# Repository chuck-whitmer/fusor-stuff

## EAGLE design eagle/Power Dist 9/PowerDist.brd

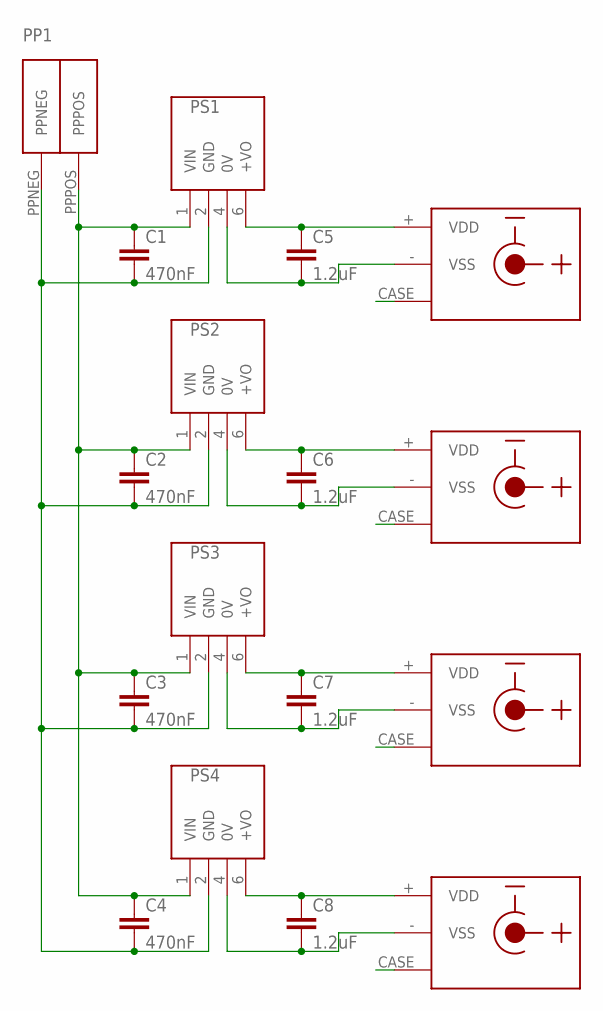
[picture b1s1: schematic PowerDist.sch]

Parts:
C1, C2, C3, C4: 470nF; C5B2.5
C5, C6, C7, C8: 1.2uF; C2.5-3
PP1: POWER_POLES_WINGS; POWERPOLE_PAIR_WINGS
PS1, PS2, PS3, PS4: PRMCE1-S12-S15-S; PRMCE1S12S15S
U$1, U$2, U$3, U$4: CUI_PJ-102A; CUI_DCJACK_PCB

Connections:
CASE: U$1.CASE
CASE1: U$2.CASE
CASE2: U$3.CASE
CASE3: U$4.CASE
unnamed: C1.1, C2.1, C3.1, C4.1, PP1.PPPOS, PS1.1 (VIN), PS2.1 (VIN), PS3.1 (VIN), PS4.1 (VIN)
unnamed: C1.2, C2.2, C3.2, C4.2, PP1.PPNEG, PS1.2 (GND), PS2.2 (GND), PS3.2 (GND), PS4.2 (GND)
unnamed: C5.1, PS1.6 (+VO), U$1.+ (VDD)
unnamed: C6.1, PS2.6 (+VO), U$2.+ (VDD)
unnamed: C7.1, PS3.6 (+VO), U$3.+ (VDD)
unnamed: C8.1, PS4.6 (+VO), U$4.+ (VDD)
unnamed: C5.2, PS1.4 (0V), U$1.- (VSS)
unnamed: C6.2, PS2.4 (0V), U$2.- (VSS)
unnamed: C7.2, PS3.4 (0V), U$3.- (VSS)
unnamed: C8.2, PS4.4 (0V), U$4.- (VSS)

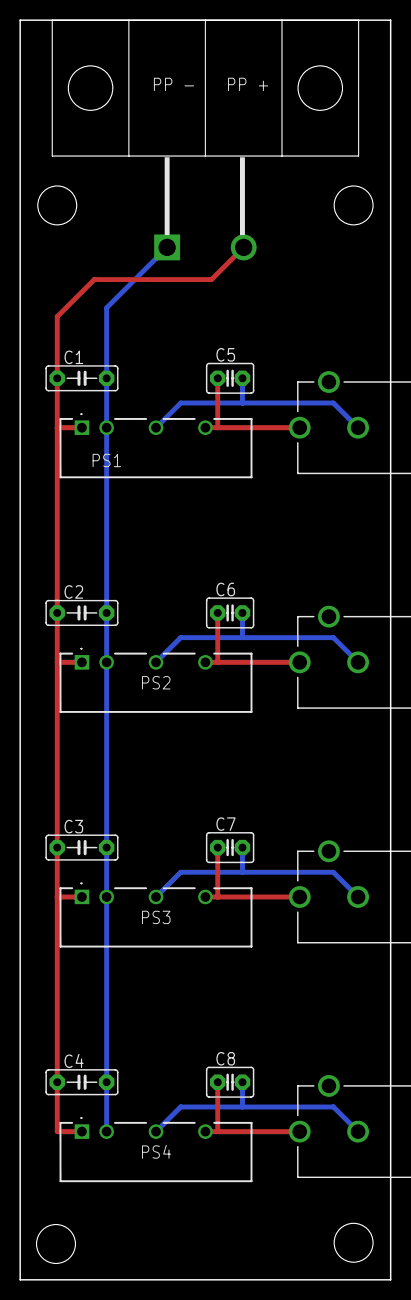
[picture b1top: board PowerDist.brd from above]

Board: 2 copper layers, 38.1 x 129.5 mm, 17 parts (0 on the bottom side), 10 nets.

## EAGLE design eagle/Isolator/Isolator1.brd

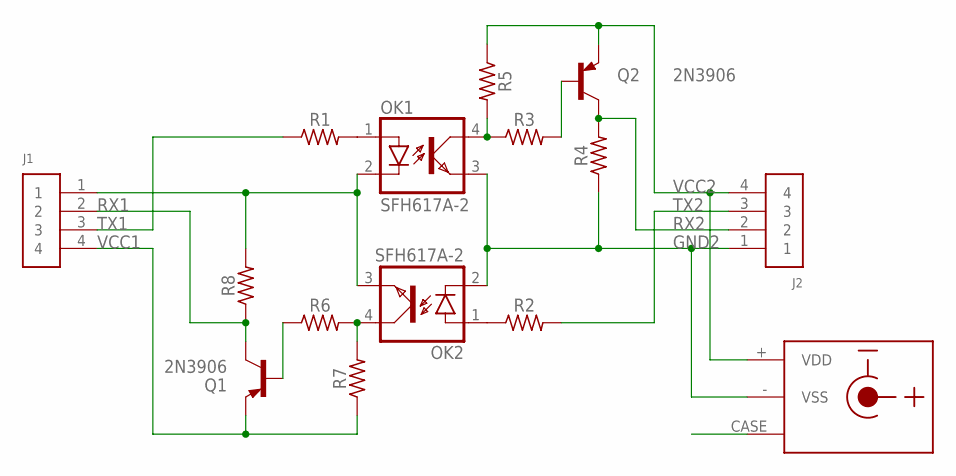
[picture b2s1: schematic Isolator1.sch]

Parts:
J1, J2: 61300411121
OK1, OK2: SFH617A-2; DIP4
Q1, Q2: 2N3906; TO92-EBC
R1, R2: 200; 0207/7
R3, R6: 1500; 0207/7
R4, R8: 1000; 0207/7
R5, R7: 75; 0207/7
U$1: CUI_PJ-102A; CUI_DCJACK_PCB

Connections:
CASE: U$1.CASE
GND1: J1.1, OK1.2 (C), OK2.3 (EMIT), R8.2
GND2: J2.1, OK1.3 (EMIT), OK2.2 (C), R4.1, U$1.- (VSS)
unnamed: OK2.1 (A), R2.1
unnamed: OK1.4 (COL), R3.1, R5.2
unnamed: Q2.B, R3.2
unnamed: OK1.1 (A), R1.2
unnamed: OK2.4 (COL), R6.2, R7.2
unnamed: Q1.B, R6.1
RX1: J1.2, Q1.C, R8.1
RX2: J2.2, Q2.C, R4.2
TX1: J1.3, R1.1
TX2: J2.3, R2.2
VCC1: J1.4, Q1.E, R7.1
VCC2: J2.4, Q2.E, R5.1, U$1.+ (VDD)

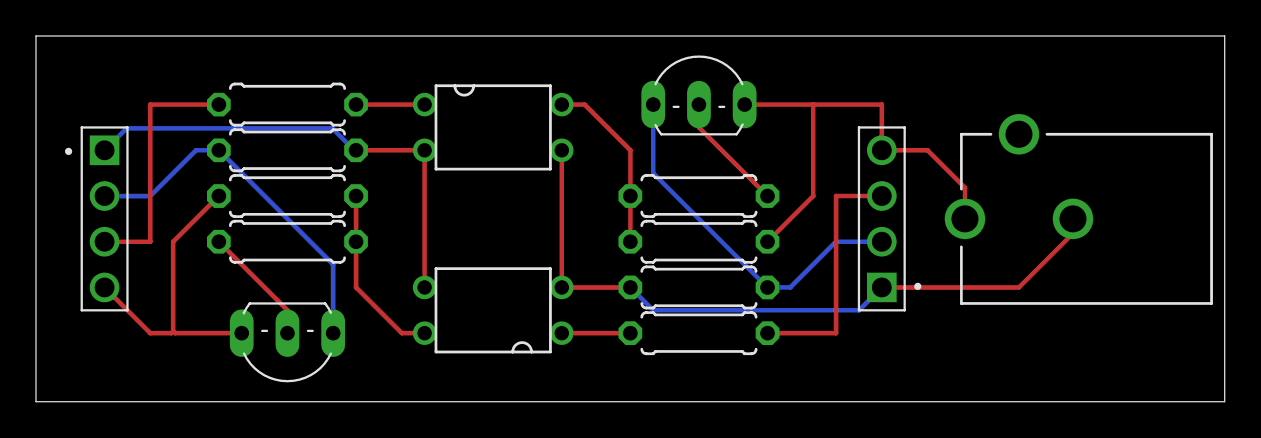
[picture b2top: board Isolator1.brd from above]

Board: 2 copper layers, 66.0 x 20.3 mm, 15 parts (0 on the bottom side), 14 nets.

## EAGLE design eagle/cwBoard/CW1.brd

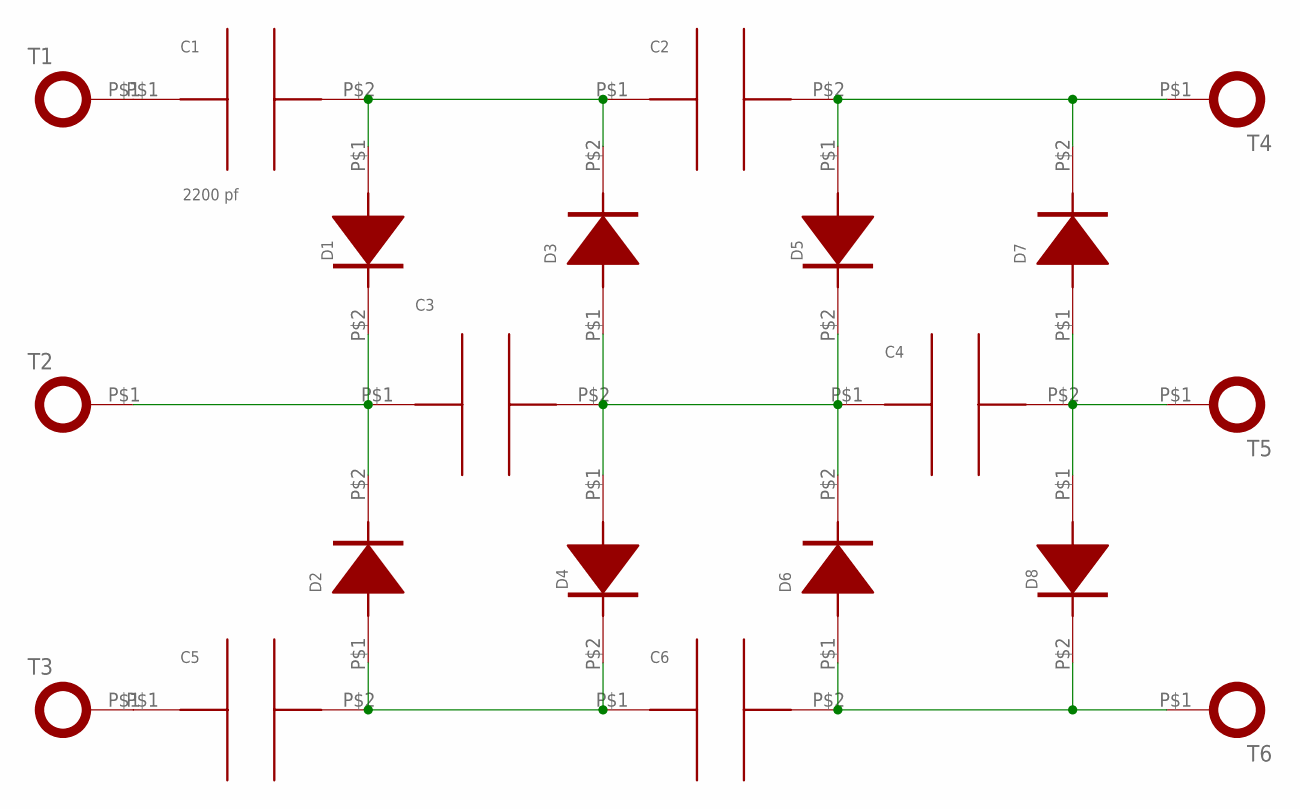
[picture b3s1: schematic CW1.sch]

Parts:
C1: 2200 pf; CAP_CT81_12
C2, C3, C4, C5, C6: HV_CAPACITOR_12MM; CAP_CT81_12
D1, D2, D3, D4, D5, D6, D7, D8: DIODE_14MM; DIODE_14
T1, T2, T3, T4, T5, T6: TERMINAL_M6; LUG_SQUARE_M6

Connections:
unnamed: C1.P$2, C2.P$1, D1.P$1 (ANODE), D3.P$2 (CATHODE)
unnamed: C3.P$1, D1.P$2 (CATHODE), D2.P$2 (CATHODE), T2.P$1
unnamed: C3.P$2, C4.P$1, D3.P$1 (ANODE), D4.P$1 (ANODE), D5.P$2 (CATHODE), D6.P$2 (CATHODE)
unnamed: C5.P$2, C6.P$1, D2.P$1 (ANODE), D4.P$2 (CATHODE)
unnamed: C6.P$2, D6.P$1 (ANODE), D8.P$2 (CATHODE), T6.P$1
unnamed: C4.P$2, D7.P$1 (ANODE), D8.P$1 (ANODE), T5.P$1
unnamed: C1.P$1, T1.P$1
unnamed: C2.P$2, D5.P$1 (ANODE), D7.P$2 (CATHODE), T4.P$1
unnamed: C5.P$1, T3.P$1

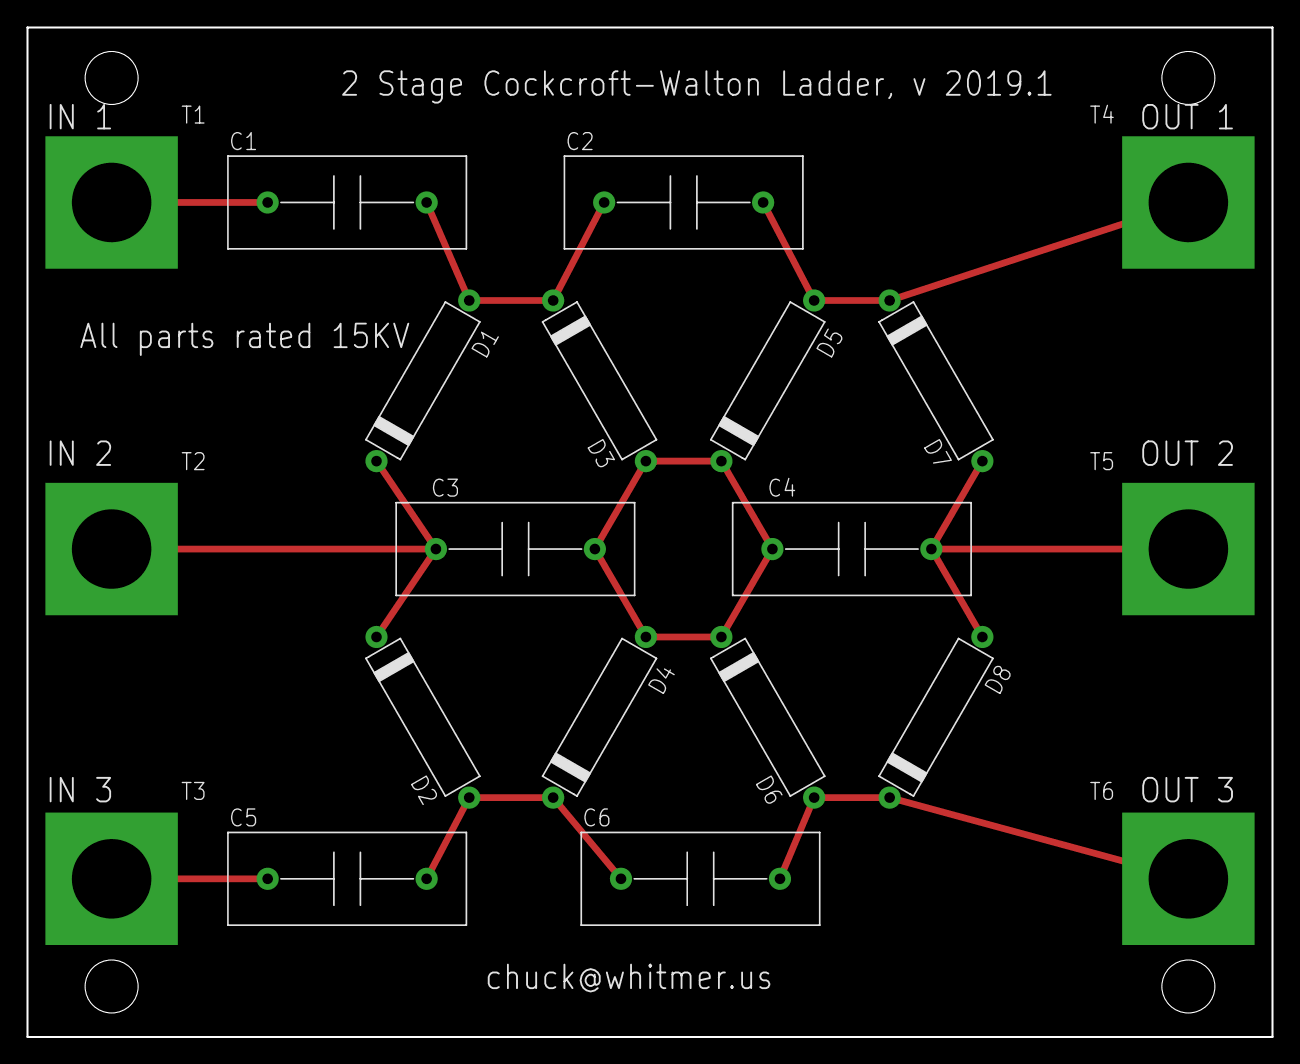
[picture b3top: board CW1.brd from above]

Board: 2 copper layers, 94.0 x 76.2 mm, 20 parts (0 on the bottom side), 9 nets.

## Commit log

2019-07-26 Fusor: Initial commits
2019-07-26 Arduino app working from laptop
2019-07-27 Added statistics class and first cut at reading ADCs
2019-08-02 Reporting voltage over bluetooth
2019-08-06 Worked for test
2019-08-08 Added simpler boards for higher current
2019-08-10 Wider spacing for 3 resistors
2019-08-17 Latest CW tests
2019-09-01 VoltageMonitor - Transmit more digits
2019-11-24 Resistor network
2019-12-05 Fusor control circuit
2020-01-28 Simplest igloo model
2020-01-28 First simulation runs
2020-01-29 Long run
2020-02-01 Reference data
2020-02-01 First part
2020-02-02 Calculations of neutron and photon energies
2020-02-21 Some plotting
2020-02-22 Added plotting
2020-02-23 Dosage
2020-02-25 Run with small gaps
2020-03-29 First wire model of grid
2020-04-09 Properly sized grid
2020-05-10 latest calc
2020-05-10 Starting on this
2020-05-13 Anodes and cathodes
2020-06-29 Latest test models
2020-06-30 Two more models
2020-07-06 Latest tests
2020-07-07 Latest
2020-07-07 Spherical detector
2020-07-08 First cut
2020-07-09 Flux MC
2020-07-14 Attempt scatterEn
2020-07-20 x3 gaussian generation
2020-07-31 Simple Neutron test with H-wax
2020-08-25 Draft 1
2020-08-26 Added software todo
2020-08-26 Small improvements
2020-08-27 Finished distribution histogram
2020-08-27 Finished section on comparing distributions
2020-08-30 Added sample fit
2020-08-30 Extra least squares stuff
2020-08-31 Linear fit example
2020-09-01 Dr Whitmer lecture
2020-09-01 Dr Whitmer lecture revised
2020-09-03 VacChamber
2020-09-13 Small tweaks
2020-10-06 Scratchpad
2020-10-07 For comparing
2021-05-23 Latest block model
2021-06-17 Geiger counter test with ascii
2021-08-09 First steps in SinFitter
2021-08-11 Added Cholesky
2021-09-10 Sine fitter
2021-09-12 Small speed improvement avoiding sumCC
2021-09-12 Tweek code for speed
2021-09-19 Starting more complex version of MC
2022-02-27 HFM shield design
2022-03-07 Latest notebooks
2022-03-19 byte1+256*byte2
2022-03-21 Start new voltage monitor
2022-03-22 Completed voltage tester
2022-03-22 One more
2022-05-01 Ioslator work
2022-05-08 New board
2022-05-08 extra
2022-05-23 Working - check power jack
2022-05-28 done
2022-07-18 Here's a repeater
2022-07-20 JSON scripts
2022-07-21 Adding json fixer
2022-07-24 latest mathematica
2022-07-25 latest mathematica for json
2022-10-17 Fit data points
2022-12-05 First version
2022-12-05 Usage
2022-12-05 static linked
2022-12-05 Update CheckSum.cpp
    We don't actually use cin and cout.

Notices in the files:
eagle/Isolator/Isolator1.brd:
Copyright (c) 2022 Whitmer Consulting LLC
